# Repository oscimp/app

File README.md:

# app
OscillatorIMP ecosystem Linux applications

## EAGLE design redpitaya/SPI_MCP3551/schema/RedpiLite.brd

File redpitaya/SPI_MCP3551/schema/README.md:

Eagle 7 CAD electronics board schematic and layout, imported into KiCAD 7
and assigned layers (top, bottom and dimensions to F.Cu, B.Cu and Edge Cuts).

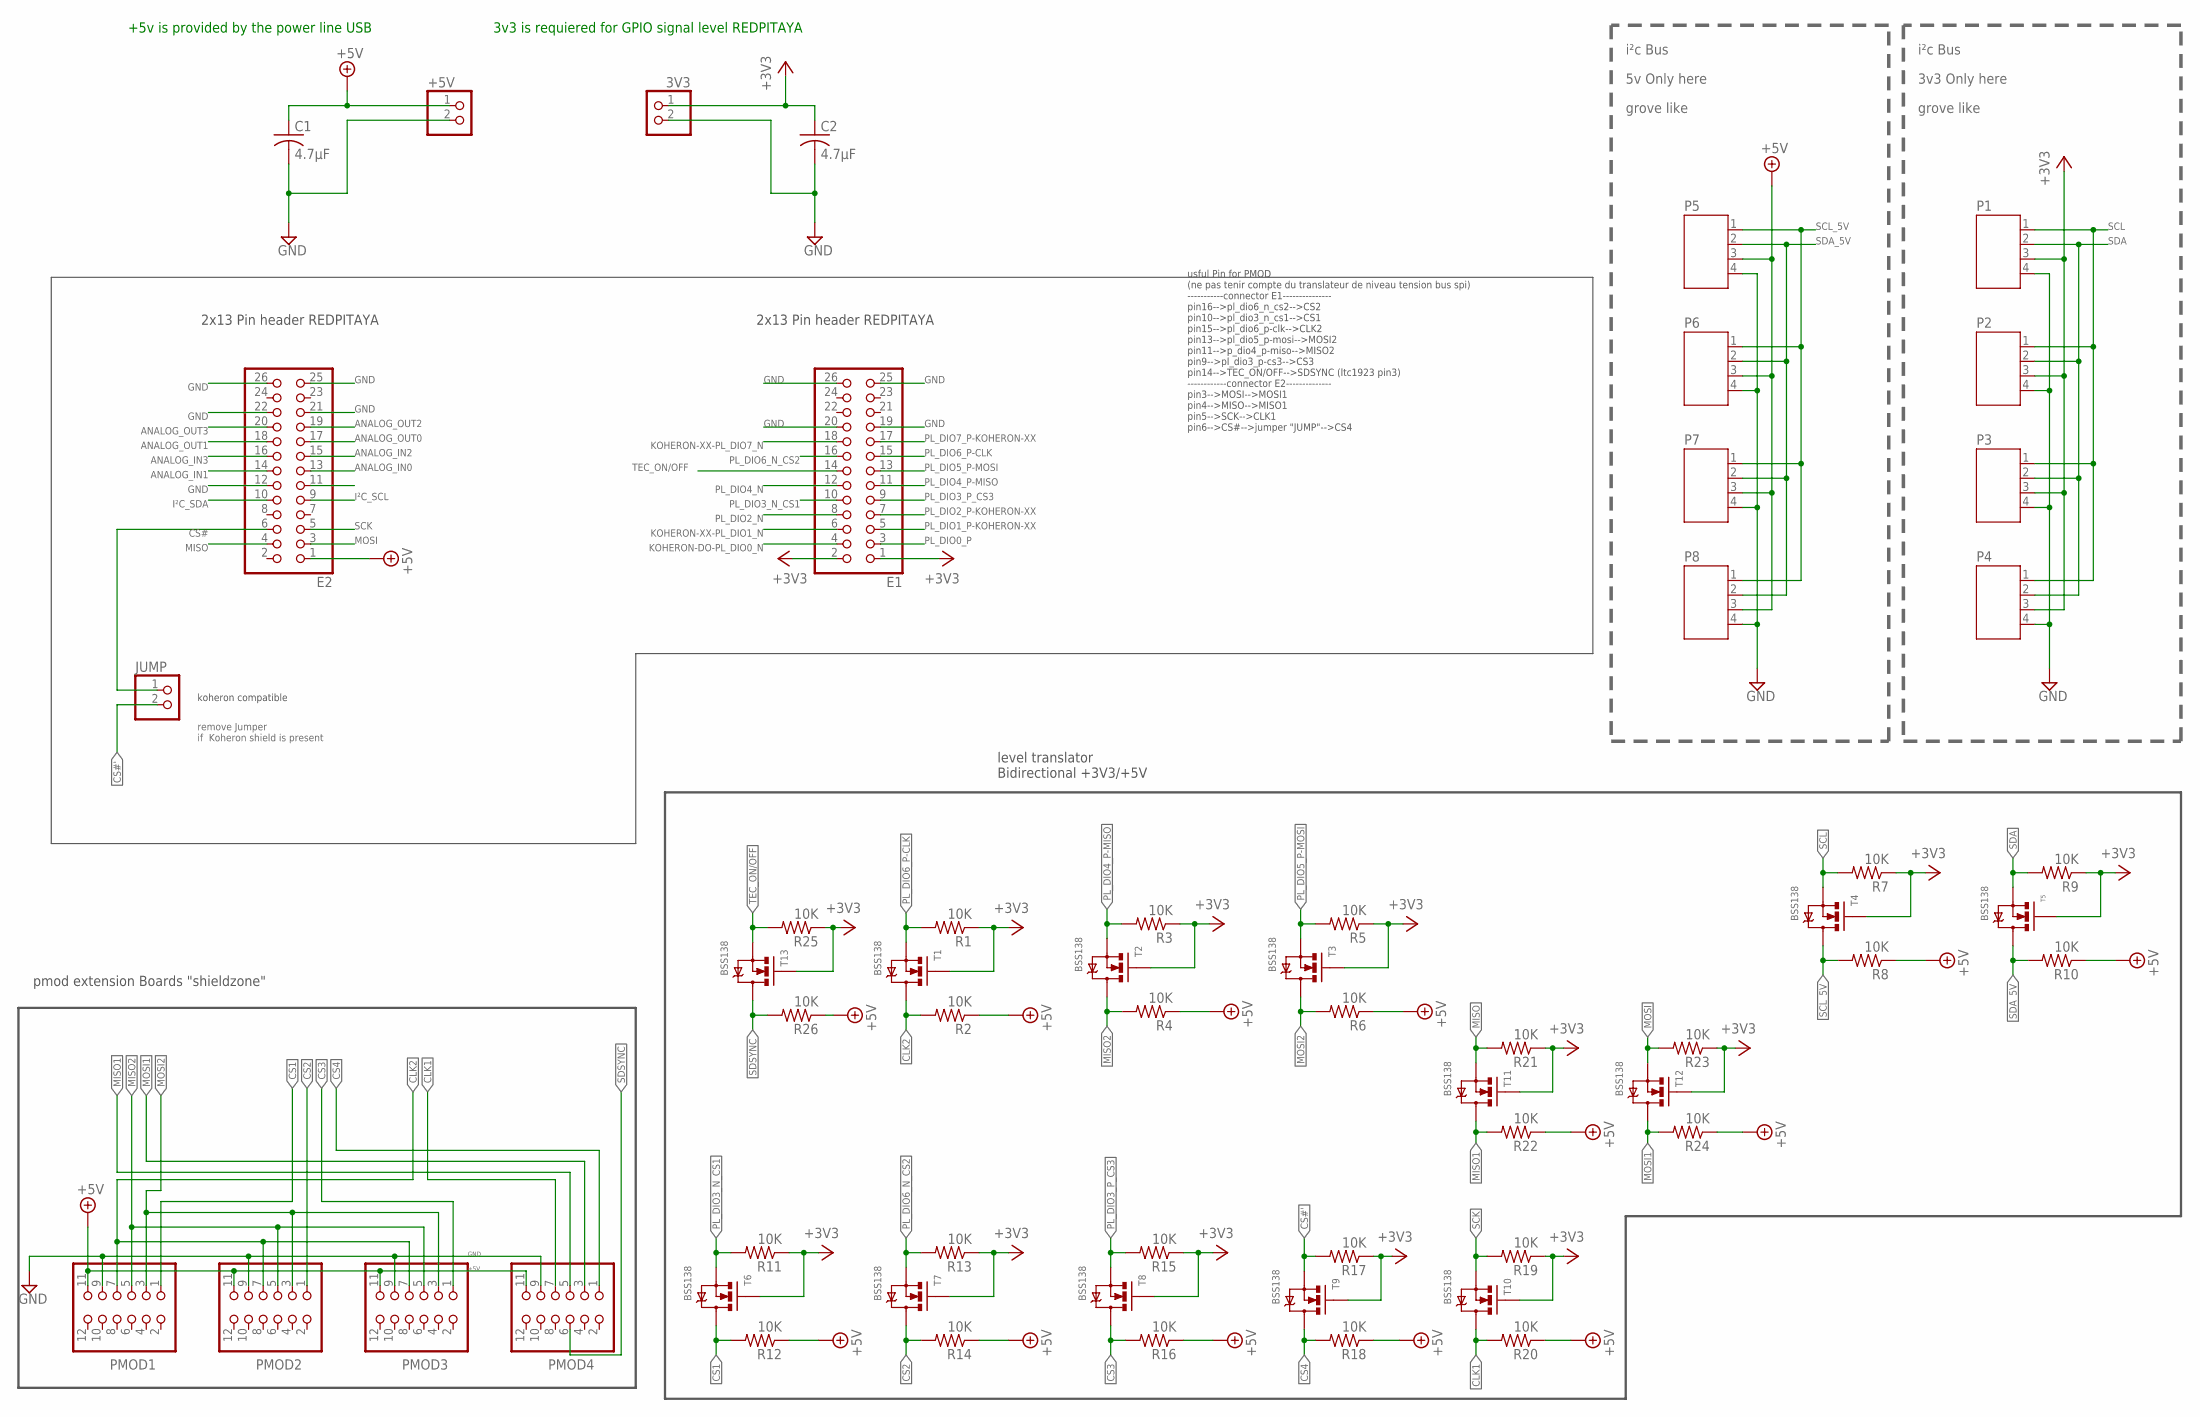
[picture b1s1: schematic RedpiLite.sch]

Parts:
3V3: PINHD-1X2; 1X02
+5V: PINHD-1X2; 1X02
C1, C2: 4.7µF; C1206
E1, E2: PINHD-2X13; 2X13
JUMP: PINHD-1X2; 1X02
P1, P2, P3, P4, P5, P6, P7, P8: JST-PH4GROVE; JST-PH4
PMOD1, PMOD2, PMOD3, PMOD4: PINHD-2X6/90; 2X06/90
R1, R2, R3, R4, R5, R6, R7, R8, R9, R10, R11, R12, R13, R14, R15, R16, R17, R18, R19, R20, R21, R22, R23, R24, R25, R26: 10K; 0603-RES
T1, T2, T3, T4, T5, T6, T7, T8, T9, T10, T11, T12, T13: BSS138; SOT23-3

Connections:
+3V3: 3V3.1, C2.1, E1.1, E1.2, P1.3, P2.3, P3.3, P4.3, R1.1, R3.1, R5.1, R7.1, R9.1, R11.1, R13.1, R15.1, R17.1, R19.1, R21.1, R23.1, R25.1, T1.1 (G), T2.1 (G), T3.1 (G), T4.1 (G), T5.1 (G), T6.1 (G), T7.1 (G), T8.1 (G), T9.1 (G), T10.1 (G), T11.1 (G), T12.1 (G), T13.1 (G)
+5V: +5V.1, C1.1, E2.1, P5.3, P6.3, P7.3, P8.3, PMOD1.11, PMOD2.11, PMOD3.11, PMOD4.11, R2.1, R4.1, R6.1, R8.1, R10.1, R12.1, R14.1, R16.1, R18.1, R20.1, R22.1, R24.1, R26.1
ANALOG_IN0: E2.13
ANALOG_IN1: E2.14
ANALOG_IN2: E2.15
ANALOG_IN3: E2.16
ANALOG_OUT0: E2.17
ANALOG_OUT1: E2.18
ANALOG_OUT2: E2.19
ANALOG_OUT3: E2.20
CLK1: PMOD4.7, R20.2, T10.3 (D)
CLK2: PMOD1.7, PMOD2.7, PMOD3.7, R2.2, T1.3 (D)
CS1: PMOD1.1, R12.2, T6.3 (D)
CS2: PMOD2.1, R14.2, T7.3 (D)
CS3: PMOD3.1, R16.2, T8.3 (D)
CS4: PMOD4.1, R18.2, T9.3 (D)
CS#: E2.6, JUMP.1
CS#': JUMP.2, R17.2, T9.2 (S)
GND: 3V3.2, +5V.2, C1.2, C2.2, E1.19, E1.20, E1.25, E1.26, E2.12, E2.21, E2.22, E2.25, E2.26, P1.4, P2.4, P3.4, P4.4, P5.4, P6.4, P7.4, P8.4, PMOD1.9, PMOD2.9, PMOD3.9, PMOD4.9
I²C_SCL: E2.9
I²C_SDA: E2.10
KOHERON-DO-PL_DIO0_N: E1.4
KOHERON-XX-PL_DIO1_N: E1.6
KOHERON-XX-PL_DIO7_N: E1.18
MISO: E2.4, R21.2, T11.2 (S)
MISO1: PMOD4.5, R22.2, T11.3 (D)
MISO2: PMOD1.5, PMOD2.5, PMOD3.5, R4.2, T2.3 (D)
MOSI: E2.3, R23.2, T12.2 (S)
MOSI1: PMOD4.3, R24.2, T12.3 (D)
MOSI2: PMOD1.3, PMOD2.3, PMOD3.3, R6.2, T3.3 (D)
PL_DIO0_P: E1.3
PL_DIO1_P-KOHERON-XX: E1.5
PL_DIO2_N: E1.8
PL_DIO2_P-KOHERON-XX: E1.7
PL_DIO3_N_CS1: E1.10, R11.2, T6.2 (S)
PL_DIO3_P_CS3: E1.9, R15.2, T8.2 (S)
PL_DIO4_N: E1.12
PL_DIO4_P-MISO: E1.11, R3.2, T2.2 (S)
PL_DIO5_P-MOSI: E1.13, R5.2, T3.2 (S)
PL_DIO6_N_CS2: E1.16, R13.2, T7.2 (S)
PL_DIO6_P-CLK: E1.15, R1.2, T1.2 (S)
PL_DIO7_P-KOHERON-XX: E1.17
SCK: E2.5, R19.2, T10.2 (S)
SCL: P1.1, P2.1, P3.1, P4.1, R7.2, T4.2 (S)
SCL_5V: P5.1, P6.1, P7.1, P8.1, R8.2, T4.3 (D)
SDA: P1.2, P2.2, P3.2, P4.2, R9.2, T5.2 (S)
SDA_5V: P5.2, P6.2, P7.2, P8.2, R10.2, T5.3 (D)
SDSYNC: PMOD4.6, R26.2, T13.3 (D)
TEC_ON/OFF: E1.14, R25.2, T13.2 (S)

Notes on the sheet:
+5v is provided by the power line USB
3v3 is requiered for GPIO signal level REDPITAYA
grove like
i²c Bus
3v3 Only here
5v Only here
koheron compatible
remove Jumper if Koheron shield is present
2x13 Pin header REDPITAYA
pmod extension Boards "shieldzone"
level translator Bidirectional +3V3/+5V
usful Pin for PMOD (ne pas tenir compte du translateur de niveau tension bus spi) -----------connector E1--------------- pin16-->pl_dio6_n_cs2-->CS2 pin10-->pl_dio3_n_cs1-->CS1 pin15-->pl_dio6_p-clk-->CLK2 pin13-->pl_dio5_p-mosi-->MOSI2 pin11-->p_dio4_p-miso-->MISO2 pin9-->pl_dio3_p-cs3-->CS3 pin14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

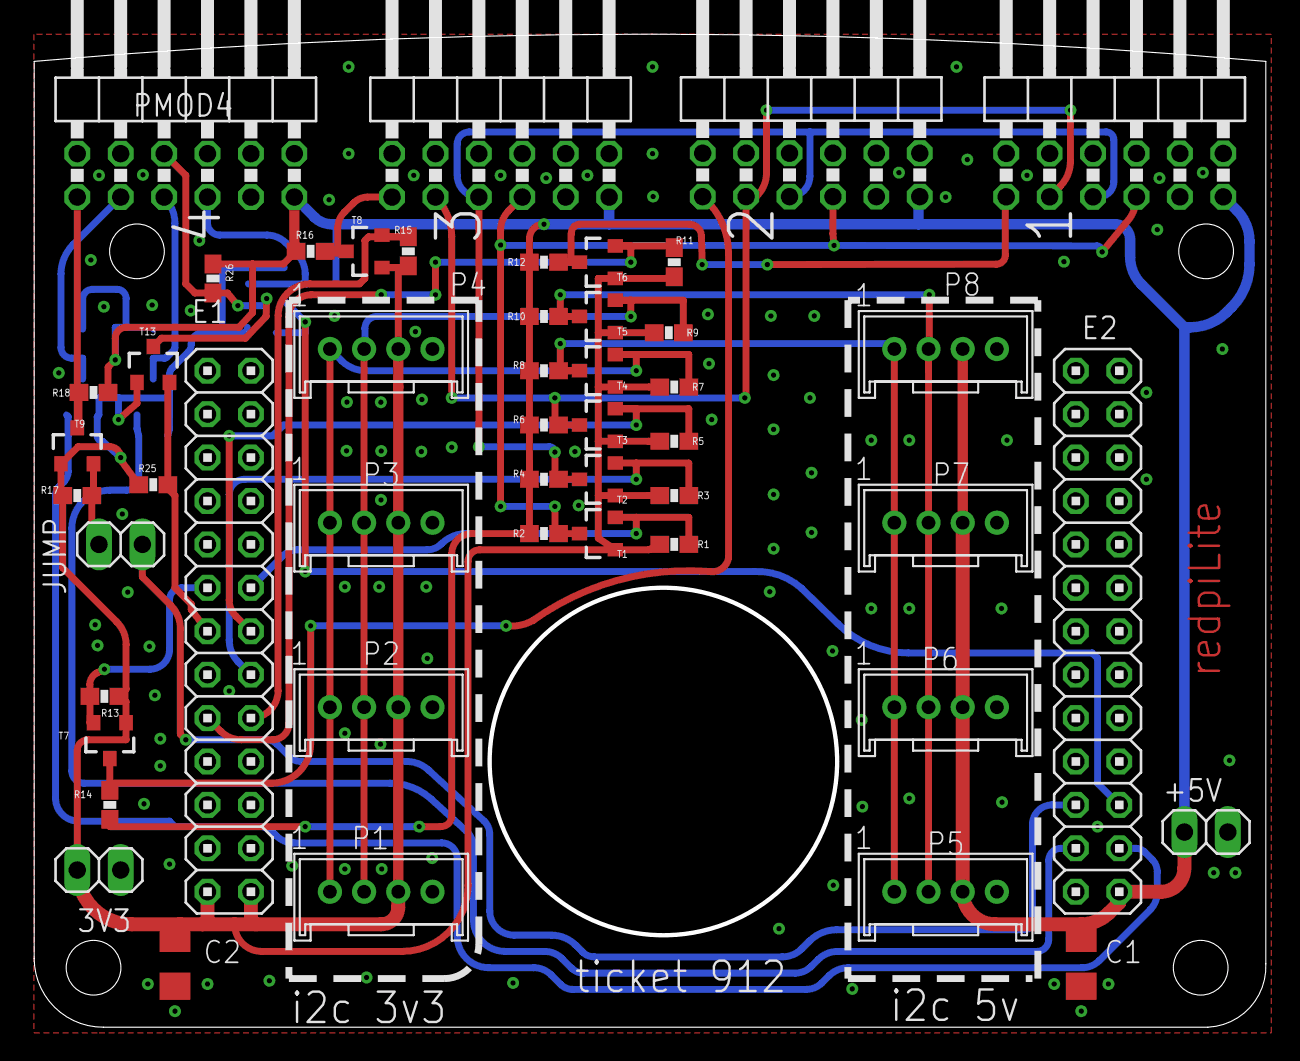
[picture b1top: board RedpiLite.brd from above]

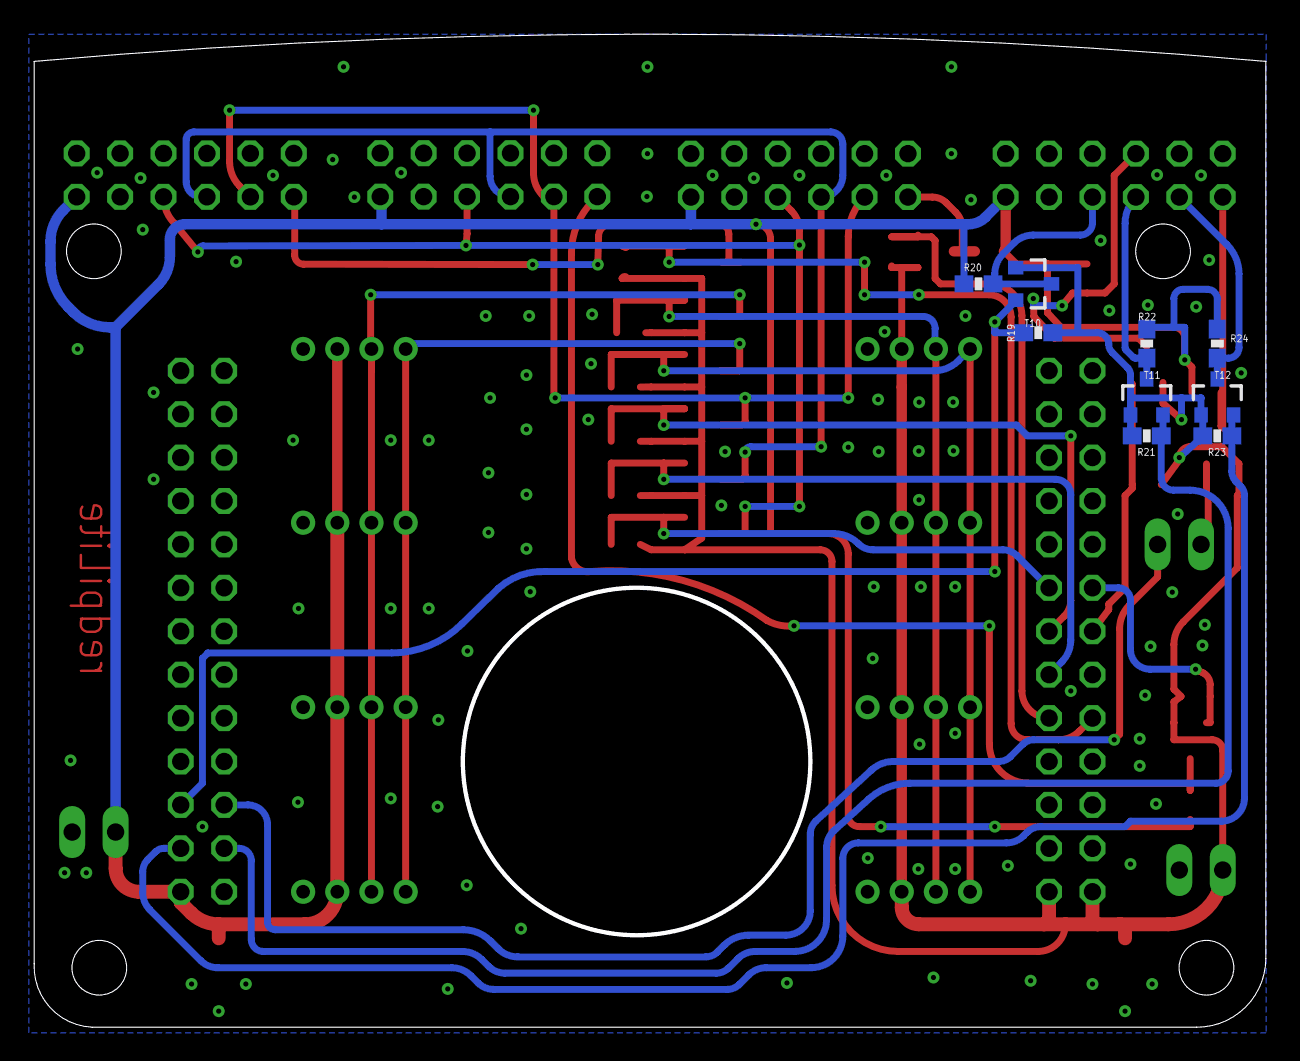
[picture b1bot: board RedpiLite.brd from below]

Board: 2 copper layers, 71.8 x 57.8 mm, 58 parts (9 on the bottom side), 30 nets.

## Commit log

2018-11-11 add setenv.sh used to export corresponding env var
2018-12-06 Adds common Makefile for userspace applications. Used to compile application, convert dts to dtb, create the target directory and install all in this directory
2018-12-14 module_generator: A tool to creates the skeleton of an userspace application (Makefile, loader script and device-tree overlay).
2018-12-20 Makefile.inc: by default (without DONT_USE_LIB set in app Makefile) link to oscimp_fpga lib
2018-12-20 module_generator: avoid infinite loop in getNodes for recursive search
2018-12-20 add option(s) node(s) to add flags or others information to Makefile
2018-12-20 module_generator: update README about options node
2018-12-20 module_generator: supress vim temporary file
2019-02-01 Makefile: creates dest directories in two call
2019-02-13 module_generator: - XML structure change (see README for new structure based on root node named project). Conserve compatibility with original structure; - uses an XML in fpga_ip to obtain witch driv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
2019-02-14 ignore vim temporary files, dtb and binaries app
2019-03-07 Makefile.inc: add staging lib to LDFLAGS
2019-03-20 add USE_STATIC_LIB var to link application with liboscimp_fpga static version
2019-03-20 module_generator: remove overlay directory only if exist
2019-03-20 module_generator: add message when success
2019-03-20 module_generator: catching polymorphic type by value
2019-06-04 module_generator: add WA for pluto (different target phandle and no bitstream to flash at runtime)
2019-06-04 Makefile.inc: add rule to install app by ssh
2019-06-15 module_generator: fix warning
2019-06-18 plutosdr: add the default design but with modifications to use oscimpDigital ecosystem
2019-07-25 Makefile.inc: add env var to install extra files
2019-12-19 Pulsed RADAR SAW sensor reader: Redpitaya application
2019-12-19 Pulsed RADAR readme file: initial commit
2019-12-19 Update README.md
    bibliography
2019-12-19 Pulsed RADAR application README
2019-12-20 Update README.md
    Hardware setup
2019-12-20 Update README.md
    application
2019-12-20 E310 based optical probe (pictures)
2019-12-20 E310 based optical probe (tree structure)
2020-01-06 module_generator: backward compatibility in Makefile generation
2020-01-07 redpitaya:pulsed_radar: update README
2020-01-08 Makefile modification + add webserver_generator
2020-01-15 redpitaya: adcChanADmaDirect: dump 1MS 16bits full speed using dma direct IP
2020-01-24 e310:optical_probe: add design and application
2020-01-24 README.md file initial commit
2020-01-29 redpitaya:adcChanADmaDirect:app: add module list in Makefile
2020-01-29 redpitaya:adcChanADmaDirect:design: drop CANDR in connect_proc and cleanup
2020-01-30 tools:module_generator: add support for intel FPGA
2020-02-16 Create README.md
    app directory README description
2020-02-16 Update README.md
    README: full sentence
2020-02-27 external ADC clocking circuit with balun
2020-03-20 massive add lock design
2020-03-20 initial README
2020-04-09 missing fir* files
2020-05-09 README.md of webserver_generator
2020-05-11 Makefile.inc: don't try to compile/install binary application when no .c file is provided
2020-09-27 include the converters for redpitaya12 SignalLab in webserver_generator
2020-09-27 add redpitaya12 adc2dac example
2020-09-28 webserver_generator update
2020-10-02 remove unnecessary files
2020-10-02 add description of adc2dac example
2020-10-02 force markdown interp
2020-10-07 corrections in webserver_generator
2020-10-08 +f0 correction in webserver_generator
2020-10-09 example design double_iq_pid_vco for redpitaya12
2020-10-19 Buttons for redpidaya_converters_12 commutators in webserver_generator
2020-10-20 check ref clock status for redpitaya_converters_12 : webserver_generator
2020-10-20 fix load of redpitaya_converters_12 param in webserver_generator
2020-10-20 webserver_generator small errors correction
2020-10-27 bad /dev for ext ref status in webserver_generator
2021-01-06 undersampling
2021-01-11 redpitaya/adcChanADmaDirect: add redpitaya16 support
2021-01-11 correction in TCL script: 2 channel connections :)
2021-01-11 README: update num channels
2021-01-19 redpitaya/double_iq_pid_vco: redpitaya16 compatibility: WIP
2021-01-19 ignore log and jou files
2021-01-27 redpitaya/double_iq_pid_vco: introduce var for size after fir
2021-01-27 redpitaya/double_iq_pid_vco: fix typo
2021-01-28 double_iq_pid_vco diagram
2021-01-28 Update README.md
    zlib dependency
2021-01-29 update web server according to library updates
2021-01-29 screenshot
2021-01-29 replace string with boolean, slider callback function with onchange.do, remove UTF8 encoding
2021-01-30 webserver_generator for remi update
2021-02-04 app/tools/module_generator/DTSGenerator: add more check
2021-02-18 correct UTF-8 (remove) encoding
2021-03-09 pidv3 setpoint is working now
2021-03-16 tools/module_generator: suppress noisy address-cells and size-cells to the fragment level
2021-03-24 webserver_generator switchReal fix
2021-04-12 tools/webserver_generator: add missing shifterComplex_dyn
2021-04-14 tools/webserver_generator: fix chmod right, fix listener with recent remi
2021-05-19 delayTempoReal_axi in webserver_generator
2021-06-11 autorun_generator -> be lazy + webserver_generator switchComplex
2021-06-11 add autorun_generator readme
2021-07-15 Makefile.inc: fix sh script name
2021-07-16 minor correction in autorun_generator
2021-07-16 update readme autorun_generator
2021-07-20 redpitaya/double_iq_pid_vco: fix webserver types
2021-07-20 webserver regeneration procedure
2021-07-21 tools/webserver_generator: fix onchange/onclick. To revert with remi 2021.3.2
2021-07-21 tools/webserver_generator: set samp_rate according to the target board
2021-07-26 nco in webserver_fenerator: fix float load error
2021-08-24 tools/webserver_generator: force python3
2021-10-12 initial commit of phaselock1CH
2021-11-19 update double_iq_pid_vco
2022-04-01 first release of comb_lock application, version 0.10
2022-04-22 hardware modification to the 14-bit redpitaya for undersampling
2022-04-22 clean backup file
2022-04-22 directory description
2022-05-05 fix driver makefile name
2022-05-05 add partial pluto support; fix remi check boxes issues
2022-05-05 make compatible with v1.1 and 2k versions of remi
2022-05-05 switch: default to False (as IP)
2022-05-12 fix nco step, add addConst size and pid_coeff_size
2022-05-20 fix f-string
2023-09-05 SPI_MCP3551 and PMOD through FPGA
2023-09-05 comment from Gwen about dts error with voltage regulator description
2023-11-14 corrected delay ip control in webserver_generator.py
2024-03-09 redpitaya125-14: design example for the dataComplex2ram and dataComplex2ram_pingpong
2024-11-25 README app data2ram
2024-11-25 rename data2ram exampe
2024-11-30 redpitaya: dataReal2ram_pingpong example
2025-03-19 fix remi update
2025-06-10 redpitaya12: add double_dds example
2025-06-13 README
2025-06-13 webserver_generator: modify GPIO from pre-6 to post-6 kernel numbering
2025-06-13 update ListView callback API
2025-06-13 double_dds: complement README
2025-06-13 update app
2025-06-16 screenshots double_iq_pid_vco
2025-12-02 tinyxml version
